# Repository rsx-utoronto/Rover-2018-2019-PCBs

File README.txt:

PCB Repo:

1. Ensure when working, the forward / back annotation is allowed. (A bar in black and yellow stripes will appear at the top of the window if the annotation has broken)
2. Do not have two people working on a board at the same time - merging is hard. (At least until we figure out how to merge nicely)

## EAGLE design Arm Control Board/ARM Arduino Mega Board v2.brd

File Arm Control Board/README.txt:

Board and Schematic for the 2018-2019 Arm control Board

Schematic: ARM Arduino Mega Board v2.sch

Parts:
ARDUINO_DUE1: ARDUINO_DUE_SHIELD
C1, C2: C-US050-045X075; C050-045X075
IC1: 7805TV; TO220V
JP1, JP2, JP3, JP4, JP5, JP12, JP13: PINHD-1X2; 1X02
LED1, LED2, LED3, LED4, LED5, LED6, LED7: LEDCHIP-LED0603; CHIP-LED0603
M-1, M-2, M-3, M-4, M-5, M-6, M-7: PINHD-1X8; 1X08
MD_OUT_1, MD_OUT_2, MD_OUT_3, MD_OUT_4, MD_OUT_5, MD_OUT_6, MD_OUT_7: PINHD-1X8; 1X08
R1, R2, R5, R6, R7, R8, R9, R12, R13, R14, R15, R16, R17, R18: 25K; R0603
R3, R4: 100K; R0603
S1, S2, S3, S4, S5, S6, S7: DS01E; DS-01
U$1: MEGA-FIT_RA_2
U$2: 14PINULTRAFIT
U$3: 4PIN_ULTRA_FIT

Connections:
3V3: ARDUINO_DUE1.3V3, S1.1, S2.1, S3.1, S4.1, S5.1, S6.1, S7.1
5V: ARDUINO_DUE1.5V0 (5V), R3.2, R4.2, U$3.PIN3
D0: ARDUINO_DUE1.0 (RX0<0), MD_OUT_7.2
D1: ARDUINO_DUE1.1 (TX0>1), MD_OUT_6.2
D2: ARDUINO_DUE1.2, MD_OUT_7.3
D3: ARDUINO_DUE1.3, MD_OUT_6.3
D4: ARDUINO_DUE1.4, MD_OUT_5.2
D5: ARDUINO_DUE1.5, MD_OUT_5.3
D6: ARDUINO_DUE1.6, MD_OUT_4.2
D7: ARDUINO_DUE1.7, MD_OUT_4.3
D8: ARDUINO_DUE1.8, MD_OUT_3.2
D9: ARDUINO_DUE1.9, MD_OUT_3.3
D10: ARDUINO_DUE1.10, MD_OUT_2.2
D11: ARDUINO_DUE1.11, MD_OUT_2.3
D12: ARDUINO_DUE1.12, MD_OUT_1.2
D13: ARDUINO_DUE1.13, MD_OUT_1.3
D14: ARDUINO_DUE1.14 (TX3_14)
D15: ARDUINO_DUE1.15 (RX3_15)
D22: ARDUINO_DUE1.22
D23: ARDUINO_DUE1.23
D24: ARDUINO_DUE1.24
D25: ARDUINO_DUE1.25
D26: ARDUINO_DUE1.26
D27: ARDUINO_DUE1.27
D28: ARDUINO_DUE1.28
D29: ARDUINO_DUE1.29
D30: ARDUINO_DUE1.30
D31: ARDUINO_DUE1.31
D32: ARDUINO_DUE1.32
D33: ARDUINO_DUE1.33
D34: ARDUINO_DUE1.34
D35: ARDUINO_DUE1.35
GND: ARDUINO_DUE1.GND, C1.2, C2.2, IC1.2 (GND), JP1.2, JP2.2, JP3.2, JP4.2, JP5.2, JP12.2, JP13.2, LED1.C, LED2.C, LED3.C, LED4.C, LED5.C, LED6.C, LED7.C, M-1.1, M-1.2, M-2.1, M-2.2, M-3.1, M-3.2, M-4.1, M-4.2, M-5.1, M-5.2, M-6.1, M-6.2, M-7.1, M-7.2, MD_OUT_1.1, MD_OUT_2.1, MD_OUT_3.1, MD_OUT_4.1, MD_OUT_5.1, MD_OUT_6.1, MD_OUT_7.1, R12.2, R13.2, R14.2, R15.2, R16.2, R17.2, R18.2, U$1.P$2, U$3.PIN1
N1: MD_OUT_2.4, R8.1, S6.2
N2: MD_OUT_3.4, R7.1, S5.2
N3: MD_OUT_4.4, R6.1, S4.2
N4: MD_OUT_5.4, R5.1, S3.2
N5: MD_OUT_6.4, R2.1, S2.2
N6: MD_OUT_7.4, R1.1, S1.2
N7: MD_OUT_1.4, R9.1, S7.2
unnamed: LED1.A, R1.2
unnamed: LED2.A, R2.2
unnamed: JP1.1, R12.1
unnamed: JP2.1, R13.1
unnamed: JP3.1, R14.1
unnamed: JP4.1, R15.1
unnamed: JP5.1, R16.1
unnamed: JP12.1, R17.1
unnamed: JP13.1, R18.1
unnamed: LED3.A, R5.2
unnamed: LED4.A, R6.2
unnamed: LED5.A, R7.2
unnamed: LED6.A, R8.2
unnamed: LED7.A, R9.2
OUTA1: M-1.5, M-1.6, U$2.PIN5
OUTA2: M-2.5, M-2.6, U$2.PIN1
OUTA3: M-3.5, M-3.6, U$2.PIN4
OUTA4: M-4.5, M-4.6, U$2.PIN8
OUTA5: M-5.5, M-5.6, U$2.PIN12
OUTA6: M-6.5, M-6.6, U$2.PIN13
OUTA7: M-7.5, M-7.6, U$2.PIN9
OUTB1: M-1.3, M-1.4, U$2.PIN7
OUTB2: M-2.3, M-2.4, U$2.PIN3
OUTB3: M-3.3, M-3.4, U$2.PIN2
OUTB4: M-4.3, M-4.4, U$2.PIN6
OUTB5: M-5.3, M-5.4, U$2.PIN10
OUTB6: M-6.3, M-6.4, U$2.PIN14
OUTB7: M-7.3, M-7.4, U$2.PIN11
SCL_OUT: ARDUINO_DUE1.21 (SCL_21), R3.1, U$3.PIN4
SDA_OUT: ARDUINO_DUE1.20 (SDA_20), R4.1, U$3.PIN2
V+: C2.1, IC1.1 (VI), M-1.7, M-1.8, M-2.7, M-2.8, M-3.7, M-3.8, M-4.7, M-4.8, M-5.7, M-5.8, M-6.7, M-6.8, M-7.7, M-7.8, U$1.P$1
VIN: ARDUINO_DUE1.VIN, C1.1, IC1.3 (VO)

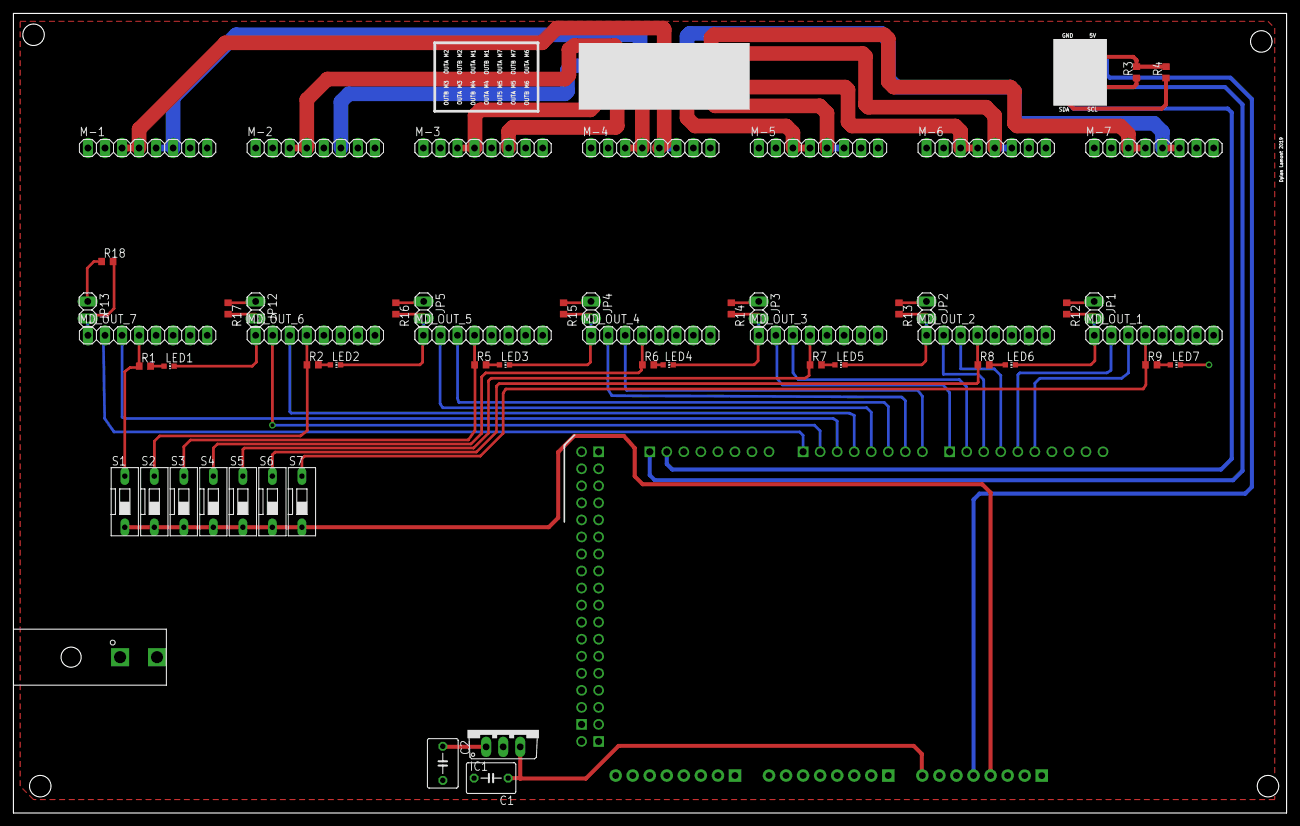
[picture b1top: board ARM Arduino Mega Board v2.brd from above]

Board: 2 copper layers, 189.8 x 119.2 mm, 58 parts (1 on the bottom side), 56 nets.

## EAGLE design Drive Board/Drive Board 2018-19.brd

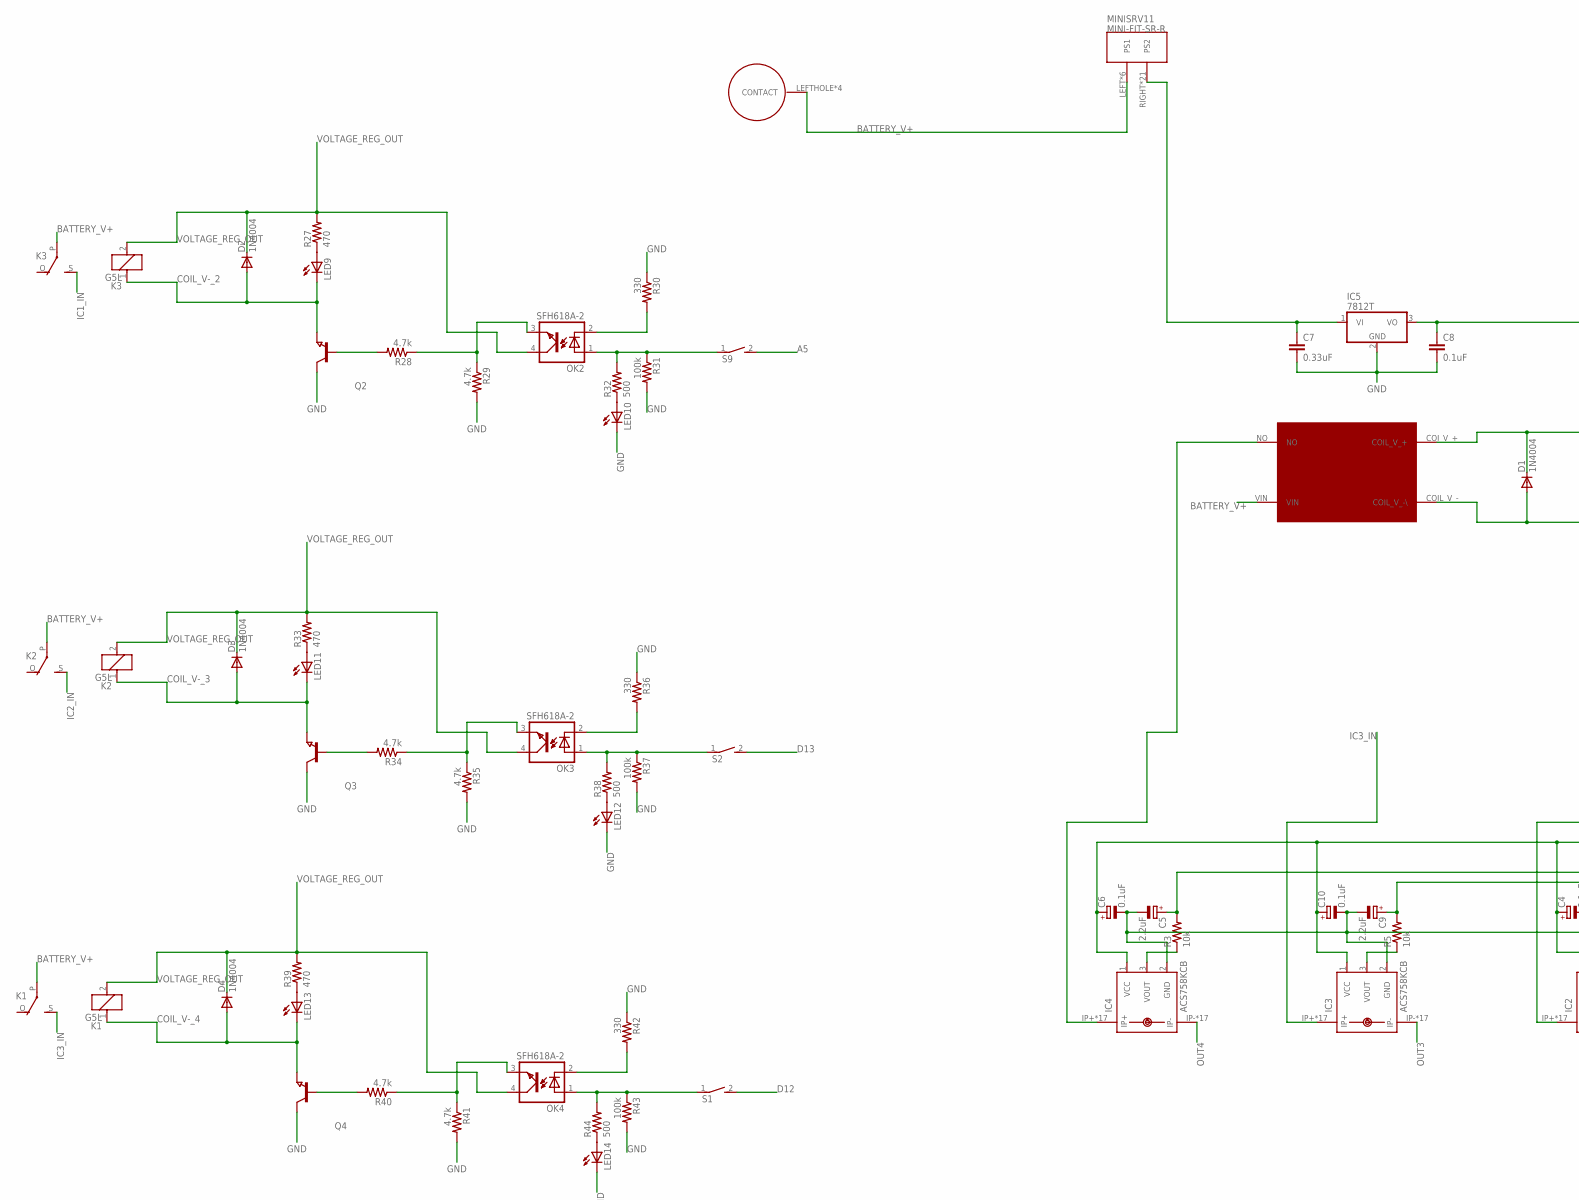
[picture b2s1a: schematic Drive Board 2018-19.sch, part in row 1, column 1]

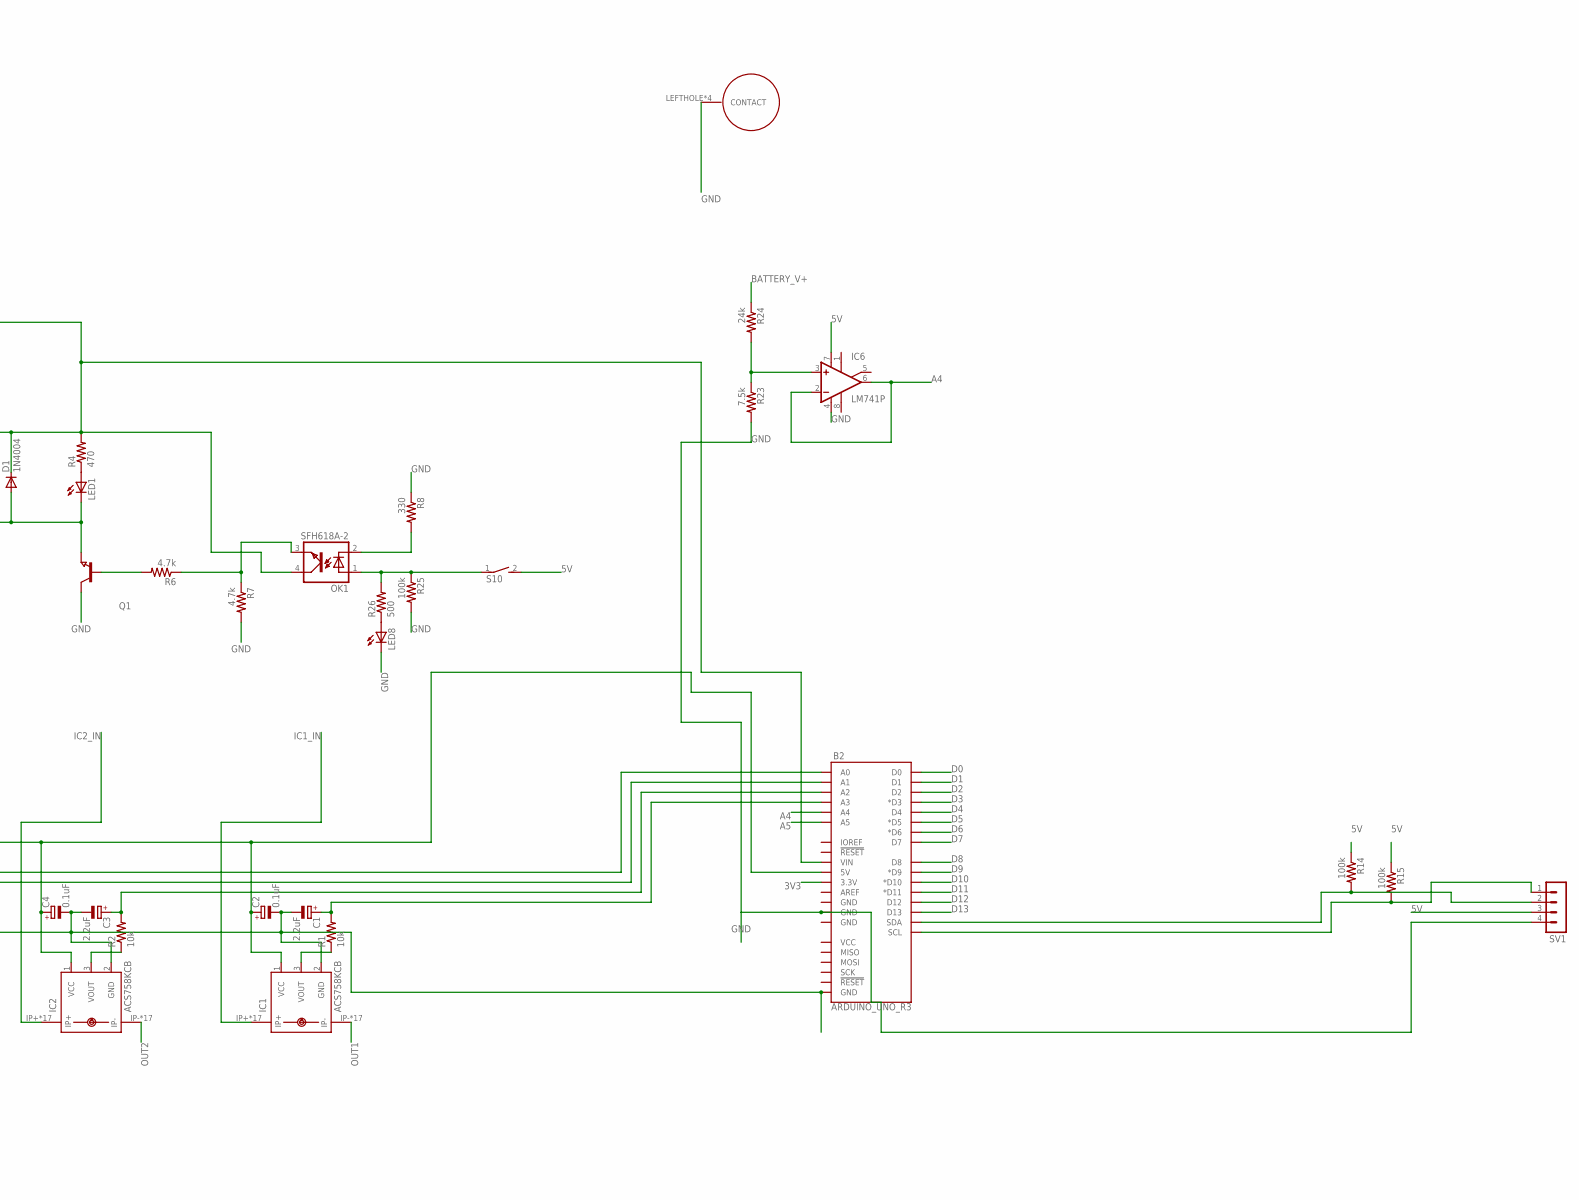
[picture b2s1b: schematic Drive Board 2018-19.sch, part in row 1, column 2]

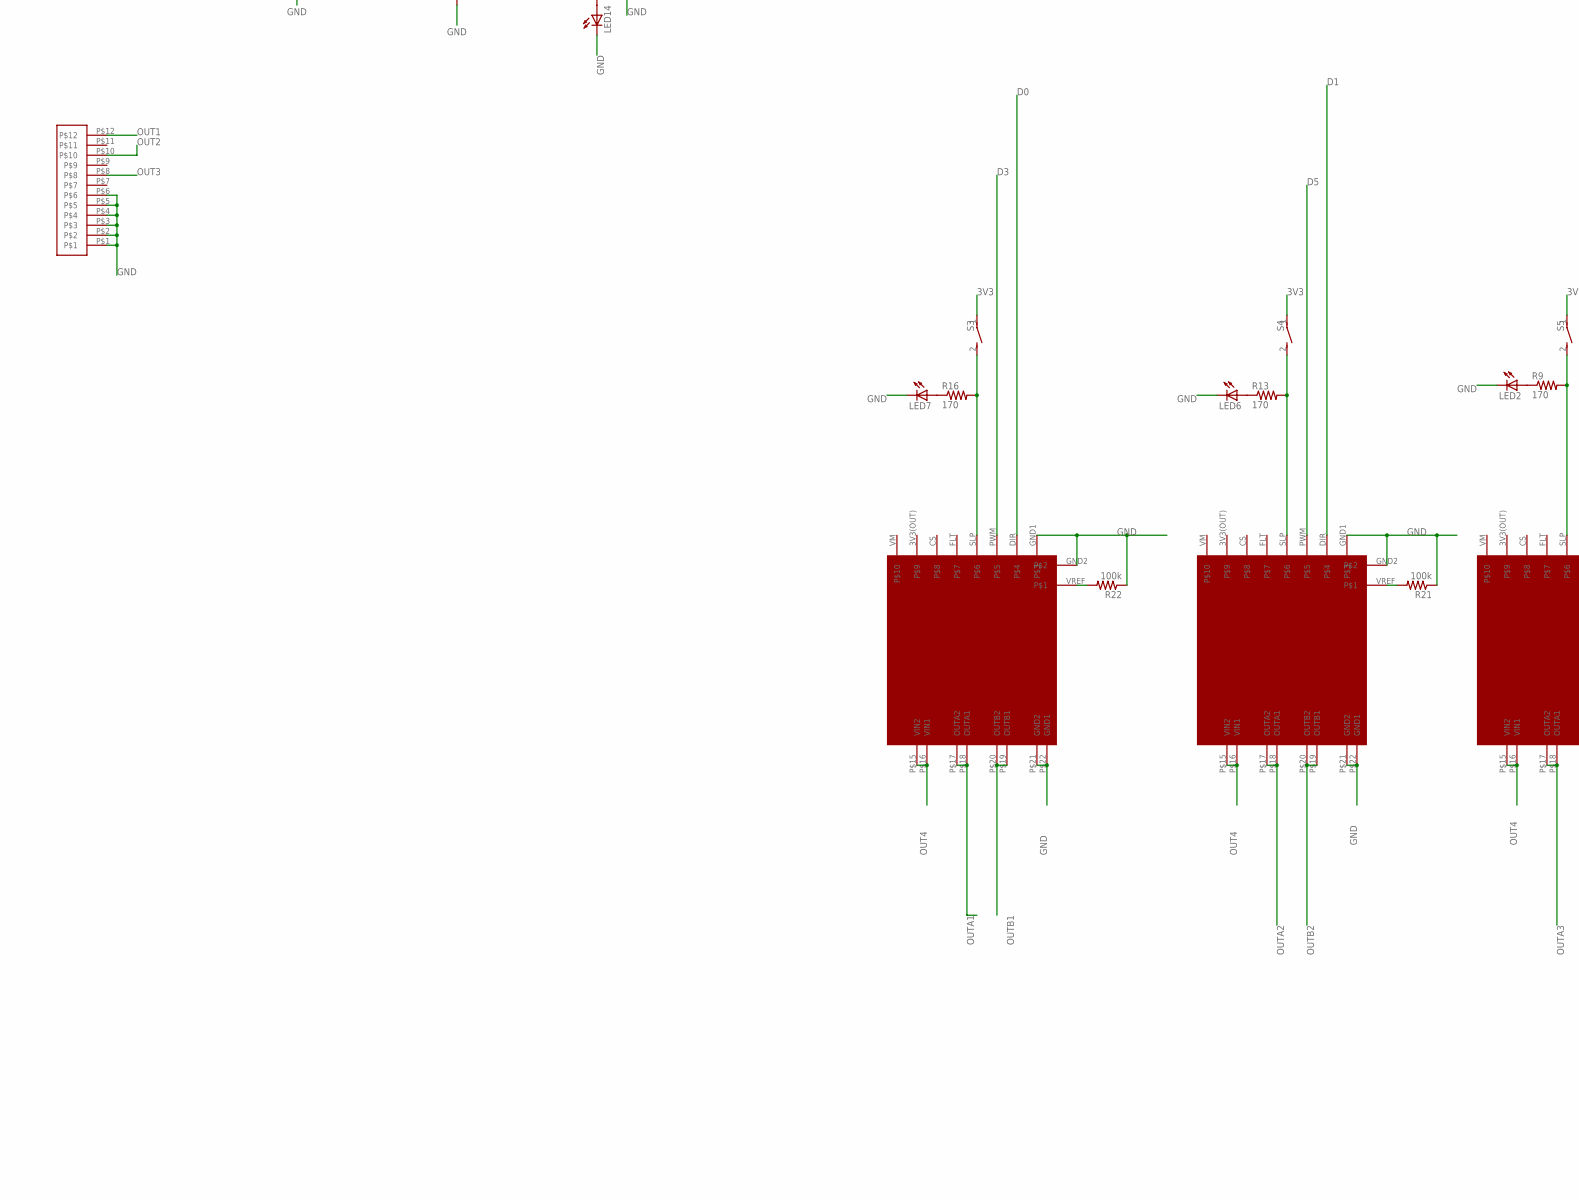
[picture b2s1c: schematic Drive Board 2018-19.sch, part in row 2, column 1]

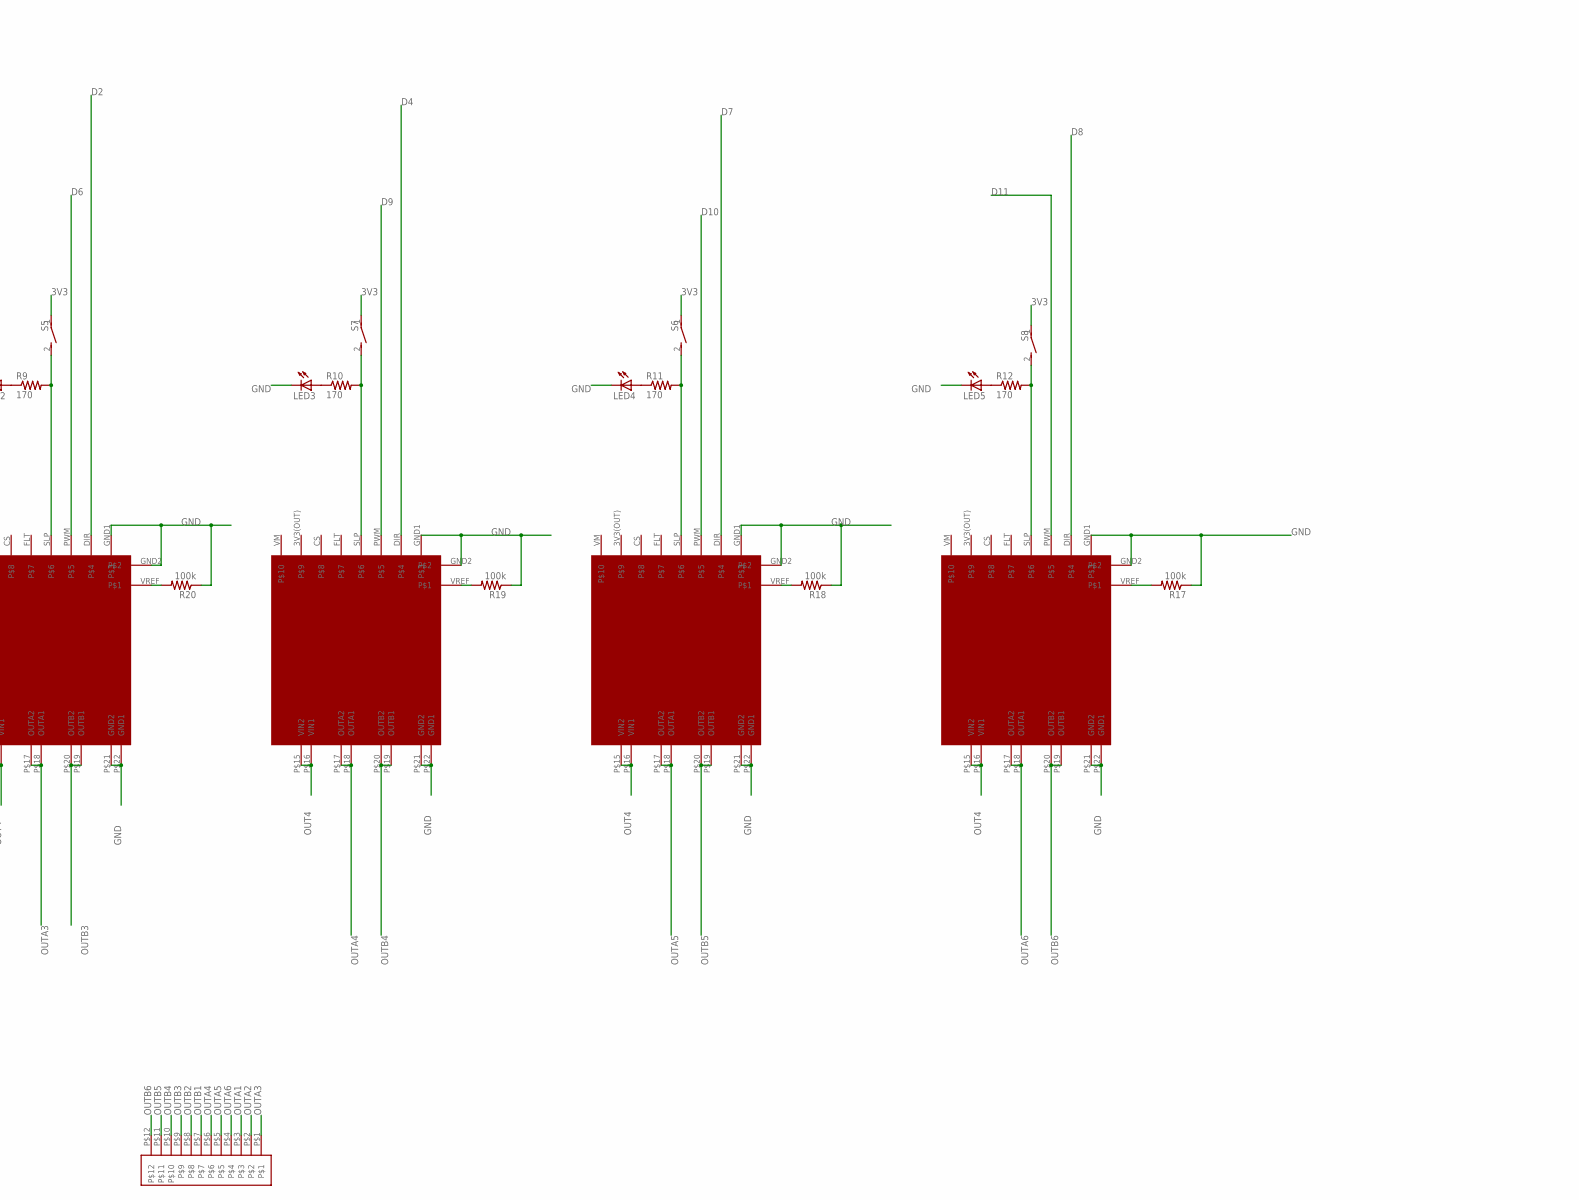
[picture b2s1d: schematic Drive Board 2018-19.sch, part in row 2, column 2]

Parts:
B2: ARDUINO_UNO_R3; ARDUINO_R3
C1, C3, C5, C9: 2.2uF; E2,5-6
C2, C4, C6, C10: 0.1uF; E2,5-6
C7: 0.33uF; C5B5.5
C8: 0.1uF; C5B5.5
D1, D2, D3, D4: 1N4004; DO41-10
IC1, IC2, IC3, IC4: ACS758KCB; CB-PFF
IC5: 7812T; TO220H
IC6: LM741P; DIL08
K1, K2, K3: G5L; G5LE
LED1, LED2, LED3, LED4, LED5, LED6, LED7, LED8, LED9, LED10, LED11, LED12, LED13, LED14: LED_E; LED_1206
MINISRV11: MINI-FIT-SR-R
OK1, OK2, OK3, OK4: SFH618A-2; DIP4
Q1, Q2, Q3, Q4: NPN-TRANSISTOR_SOT23; SOT23
R1, R2, R3, R5: 10k; 0204/7
R4, R27, R33, R39: 470; 0207/10
R6, R7, R28, R29, R34, R35, R40, R41: 4.7k; 0207/10
R8, R30, R36, R42: 330; 0207/10
R9, R10, R11, R12, R13, R16: 170; 0207/10
R14, R15, R17, R18, R19, R20, R21, R22, R25, R31, R37, R43: 100k; 0207/10
R23: 7.5k; 0207/10
R24: 24k; 0207/10
R26, R32, R38, R44: 500; 0207/10
S1, S2, S3, S4, S5, S6, S7, S8, S9, S10: DS01E; DS-01
SV1: MA04-1
U$1, U$2, U$3, U$4, U$5, U$6: HPMD18V17
U$7, U$9: BUSBAR_MOUNT
U$11: JTN1AS-PA-F-DC12V
U$12, U$13: MEGA-FIT_RA_12

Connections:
3V3: B2.3.3V, S3.1, S4.1, S5.1, S6.1, S7.1, S8.1
5V: B2.5V, C2.+, C4.+, C6.+, C10.+, IC1.1 (VCC), IC2.1 (VCC), IC3.1 (VCC), IC4.1 (VCC), IC6.7 (V+), R14.1, R15.1, S10.2, SV1.3
A4: B2.A4, IC6.2 (-IN), IC6.6 (OUT)
A5: B2.A5, S9.2
BATTERY_V+: K1.P, K2.P, K3.P, MINISRV11.LEFT (PS1), MINISRV11.LEFT@1 (PS1), MINISRV11.LEFT@2 (PS1), MINISRV11.LEFT@3 (PS1), MINISRV11.LEFT@4 (PS1), MINISRV11.LEFT@5 (PS1), R24.1, U$7.LEFTHOLE, U$7.P$1, U$7.P$2, U$7.RIGHTHOLE, U$11.VIN
COIL_V-_1: D1.A, LED1.C, Q1.2 (E), U$11.COIL_V_- (COIL_V_-\)
COIL_V-_2: D2.A, K3.1, LED9.C, Q2.2 (E)
COIL_V-_3: D3.A, K2.1, LED11.C, Q3.2 (E)
COIL_V-_4: D4.A, K1.1, LED13.C, Q4.2 (E)
D0: B2.D0, U$1.DIR
D1: B2.D1, U$2.DIR
D2: B2.D2, U$3.DIR
D3: B2.D3 (*D3), U$1.PWM
D4: B2.D4, U$4.DIR
D5: B2.D5 (*D5), U$2.PWM
D6: B2.D6 (*D6), U$3.PWM
D7: B2.D7, U$5.DIR
D8: B2.D8, U$6.DIR
D9: B2.D9 (*D9), U$4.PWM
D10: B2.D10 (*D10), U$5.PWM
D11: B2.D11 (*D11), U$6.PWM
D12: B2.D12, S1.2
D13: B2.D13, S2.2
ESTOP: C7.1, IC5.1 (VI), MINISRV11.RIGHT (PS2), MINISRV11.RIGHT@1 (PS2), MINISRV11.RIGHT@2 (PS2), MINISRV11.RIGHT@3 (PS2), MINISRV11.RIGHT@4 (PS2), MINISRV11.RIGHT@5 (PS2), MINISRV11.RIGHT@6 (PS2), MINISRV11.RIGHT@7 (PS2), MINISRV11.RIGHT@8 (PS2), MINISRV11.RIGHT@9 (PS2), MINISRV11.RIGHT@10 (PS2), MINISRV11.RIGHT@11 (PS2), MINISRV11.RIGHT@12 (PS2), MINISRV11.RIGHT@13 (PS2), MINISRV11.RIGHT@14 (PS2), MINISRV11.RIGHT@15 (PS2), MINISRV11.RIGHT@16 (PS2), MINISRV11.RIGHT@17 (PS2), MINISRV11.RIGHT@18 (PS2), MINISRV11.RIGHT@19 (PS2), MINISRV11.RIGHT@20 (PS2)
GND: B2.GND@1 (GND), B2.GND@3 (GND), C1.-, C2.-, C3.-, C4.-, C5.-, C6.-, C7.2, C8.2, C9.-, C10.-, IC1.2 (GND), IC2.2 (GND), IC3.2 (GND), IC4.2 (GND), IC5.2 (GND), IC6.4 (V-), LED2.C, LED3.C, LED4.C, LED5.C, LED6.C, LED7.C, LED8.C, LED10.C, LED12.C, LED14.C, Q1.3 (C), Q2.3 (C), Q3.3 (C), Q4.3 (C), R7.2, R8.1, R17.1, R18.1, R19.1, R20.1, R21.1, R22.1, R23.2, R25.2, R29.2, R30.1, R31.2, R35.2, R36.1, R37.2, R41.2, R42.1, R43.2, SV1.4, U$1.GND1, U$1.GND2, U$1.P$21 (GND2), U$1.P$22 (GND1), U$2.GND1, U$2.GND2, U$2.P$21 (GND2), U$2.P$22 (GND1), U$3.GND1, U$3.GND2, U$3.P$21 (GND2), U$3.P$22 (GND1), U$4.GND1, U$4.GND2, U$4.P$21 (GND2), U$4.P$22 (GND1), U$5.GND1, U$5.GND2, U$5.P$21 (GND2), U$5.P$22 (GND1), U$6.GND1, U$6.GND2, U$6.P$21 (GND2), U$6.P$22 (GND1), U$9.LEFTHOLE, U$9.P$1, U$9.P$2, U$9.RIGHTHOLE, U$13.P$1, U$13.P$2, U$13.P$3, U$13.P$4, U$13.P$5, U$13.P$6
IC1_IN: IC1.IP+, IC1.IP+@2 (IP+), IC1.IP+@3 (IP+), IC1.IP+@4 (IP+), IC1.IP+@5 (IP+), IC1.IP+@6 (IP+), IC1.IP+@7 (IP+), IC1.IP+@8 (IP+), IC1.IP+@9 (IP+), IC1.IP+@10 (IP+), IC1.IP+@11 (IP+), IC1.IP+@12 (IP+), IC1.IP+@13 (IP+), IC1.IP+@14 (IP+), IC1.IP+@15 (IP+), IC1.IP+@16 (IP+), IC1.IP+@17 (IP+), K3.S
IC2_IN: IC2.IP+, IC2.IP+@2 (IP+), IC2.IP+@3 (IP+), IC2.IP+@4 (IP+), IC2.IP+@5 (IP+), IC2.IP+@6 (IP+), IC2.IP+@7 (IP+), IC2.IP+@8 (IP+), IC2.IP+@9 (IP+), IC2.IP+@10 (IP+), IC2.IP+@11 (IP+), IC2.IP+@12 (IP+), IC2.IP+@13 (IP+), IC2.IP+@14 (IP+), IC2.IP+@15 (IP+), IC2.IP+@16 (IP+), IC2.IP+@17 (IP+), K2.S
IC3_IN: IC3.IP+, IC3.IP+@2 (IP+), IC3.IP+@3 (IP+), IC3.IP+@4 (IP+), IC3.IP+@5 (IP+), IC3.IP+@6 (IP+), IC3.IP+@7 (IP+), IC3.IP+@8 (IP+), IC3.IP+@9 (IP+), IC3.IP+@10 (IP+), IC3.IP+@11 (IP+), IC3.IP+@12 (IP+), IC3.IP+@13 (IP+), IC3.IP+@14 (IP+), IC3.IP+@15 (IP+), IC3.IP+@16 (IP+), IC3.IP+@17 (IP+), K1.S
unnamed: LED8.A, R26.1
unnamed: IC1.3 (VOUT), R1.1
unnamed: LED1.A, R4.1
unnamed: B2.A3, C1.+, R1.2
unnamed: IC6.3 (+IN), R23.1, R24.2
unnamed: IC2.3 (VOUT), R2.1
unnamed: LED9.A, R27.1
unnamed: B2.A2, C3.+, R2.2
unnamed: Q2.1 (B), R28.2
unnamed: IC4.3 (VOUT), R3.1
unnamed: OK2.3 (EMIT), R28.1, R29.1
unnamed: OK2.2 (C), R30.2
unnamed: B2.A1, C9.+, R5.2
unnamed: LED10.A, R32.1
unnamed: LED11.A, R33.1
unnamed: Q1.1 (B), R6.2
unnamed: IC3.3 (VOUT), R5.1
unnamed: Q3.1 (B), R34.2
unnamed: B2.A0, C5.+, R3.2
unnamed: OK3.3 (EMIT), R34.1, R35.1
unnamed: OK1.3 (EMIT), R6.1, R7.1
unnamed: OK3.2 (C), R36.2
unnamed: LED12.A, R38.1
unnamed: IC4.IP+, IC4.IP+@2 (IP+), IC4.IP+@3 (IP+), IC4.IP+@4 (IP+), IC4.IP+@5 (IP+), IC4.IP+@6 (IP+), IC4.IP+@7 (IP+), IC4.IP+@8 (IP+), IC4.IP+@9 (IP+), IC4.IP+@10 (IP+), IC4.IP+@11 (IP+), IC4.IP+@12 (IP+), IC4.IP+@13 (IP+), IC4.IP+@14 (IP+), IC4.IP+@15 (IP+), IC4.IP+@16 (IP+), IC4.IP+@17 (IP+), U$11.NO
unnamed: LED13.A, R39.1
unnamed: Q4.1 (B), R40.2
unnamed: OK4.3 (EMIT), R40.1, R41.1
unnamed: OK4.2 (C), R42.2
unnamed: LED14.A, R44.1
unnamed: OK1.2 (C), R8.2
unnamed: R18.2, U$5.VREF
unnamed: R20.2, U$3.VREF
unnamed: LED2.A, R9.1
unnamed: R17.2, U$6.VREF
unnamed: B2.SCL, R15.2, SV1.1
unnamed: B2.SDA, R14.2, SV1.2
unnamed: LED3.A, R10.1
unnamed: LED4.A, R11.1
unnamed: LED5.A, R12.1
unnamed: R19.2, U$4.VREF
unnamed: LED6.A, R13.1
unnamed: LED7.A, R16.1
unnamed: R21.2, U$2.VREF
unnamed: R22.2, U$1.VREF
unnamed: R12.2, S8.2, U$6.SLP
unnamed: R11.2, S6.2, U$5.SLP
unnamed: R10.2, S7.2, U$4.SLP
unnamed: R9.2, S5.2, U$3.SLP
unnamed: R13.2, S4.2, U$2.SLP
unnamed: R16.2, S3.2, U$1.SLP
OPTO1: OK2.1 (A), R31.1, R32.2, S9.1
OPTO2: OK3.1 (A), R37.1, R38.2, S2.1
OPTO3: OK4.1 (A), R43.1, R44.2, S1.1
OPTO4: OK1.1 (A), R25.1, R26.2, S10.1
OUT1: IC1.IP-, IC1.IP-@2 (IP-), IC1.IP-@3 (IP-), IC1.IP-@4 (IP-), IC1.IP-@5 (IP-), IC1.IP-@6 (IP-), IC1.IP-@7 (IP-), IC1.IP-@8 (IP-), IC1.IP-@9 (IP-), IC1.IP-@10 (IP-), IC1.IP-@11 (IP-), IC1.IP-@12 (IP-), IC1.IP-@13 (IP-), IC1.IP-@14 (IP-), IC1.IP-@15 (IP-), IC1.IP-@16 (IP-), IC1.IP-@17 (IP-), U$13.P$12
OUT2: IC2.IP-, IC2.IP-@2 (IP-), IC2.IP-@3 (IP-), IC2.IP-@4 (IP-), IC2.IP-@5 (IP-), IC2.IP-@6 (IP-), IC2.IP-@7 (IP-), IC2.IP-@8 (IP-), IC2.IP-@9 (IP-), IC2.IP-@10 (IP-), IC2.IP-@11 (IP-), IC2.IP-@12 (IP-), IC2.IP-@13 (IP-), IC2.IP-@14 (IP-), IC2.IP-@15 (IP-), IC2.IP-@16 (IP-), IC2.IP-@17 (IP-), U$13.P$10
OUT3: IC3.IP-, IC3.IP-@2 (IP-), IC3.IP-@3 (IP-), IC3.IP-@4 (IP-), IC3.IP-@5 (IP-), IC3.IP-@6 (IP-), IC3.IP-@7 (IP-), IC3.IP-@8 (IP-), IC3.IP-@9 (IP-), IC3.IP-@10 (IP-), IC3.IP-@11 (IP-), IC3.IP-@12 (IP-), IC3.IP-@13 (IP-), IC3.IP-@14 (IP-), IC3.IP-@15 (IP-), IC3.IP-@16 (IP-), IC3.IP-@17 (IP-), U$13.P$8
OUT4: IC4.IP-, IC4.IP-@2 (IP-), IC4.IP-@3 (IP-), IC4.IP-@4 (IP-), IC4.IP-@5 (IP-), IC4.IP-@6 (IP-), IC4.IP-@7 (IP-), IC4.IP-@8 (IP-), IC4.IP-@9 (IP-), IC4.IP-@10 (IP-), IC4.IP-@11 (IP-), IC4.IP-@12 (IP-), IC4.IP-@13 (IP-), IC4.IP-@14 (IP-), IC4.IP-@15 (IP-), IC4.IP-@16 (IP-), IC4.IP-@17 (IP-), U$1.P$15 (VIN2), U$1.P$16 (VIN1), U$2.P$15 (VIN2), U$2.P$16 (VIN1), U$3.P$15 (VIN2), U$3.P$16 (VIN1), U$4.P$15 (VIN2), U$4.P$16 (VIN1), U$5.P$15 (VIN2), U$5.P$16 (VIN1), U$6.P$15 (VIN2), U$6.P$16 (VIN1)
OUTA1: U$1.P$17 (OUTA2), U$1.P$18 (OUTA1), U$12.P$3
OUTA2: U$2.P$17 (OUTA2), U$2.P$18 (OUTA1), U$12.P$2
OUTA3: U$3.P$17 (OUTA2), U$3.P$18 (OUTA1), U$12.P$1
OUTA4: U$4.P$17 (OUTA2), U$4.P$18 (OUTA1), U$12.P$6
OUTA5: U$5.P$17 (OUTA2), U$5.P$18 (OUTA1), U$12.P$5
OUTA6: U$6.P$17 (OUTA2), U$6.P$18 (OUTA1), U$12.P$4
OUTB1: U$1.P$19 (OUTB1), U$1.P$20 (OUTB2), U$12.P$7
OUTB2: U$2.P$19 (OUTB1), U$2.P$20 (OUTB2), U$12.P$8
OUTB3: U$3.P$19 (OUTB1), U$3.P$20 (OUTB2), U$12.P$9
OUTB4: U$4.P$19 (OUTB1), U$4.P$20 (OUTB2), U$12.P$10
OUTB5: U$5.P$19 (OUTB1), U$5.P$20 (OUTB2), U$12.P$11
OUTB6: U$6.P$19 (OUTB1), U$6.P$20 (OUTB2), U$12.P$12
VOLTAGE_REG_OUT: B2.VIN, C8.1, D1.C, D2.C, D3.C, D4.C, IC5.3 (VO), K1.2, K2.2, K3.2, OK1.4 (COL), OK2.4 (COL), OK3.4 (COL), OK4.4 (COL), R4.2, R27.2, R33.2, R39.2, U$11.COI_V_+ (COIL_V_+)

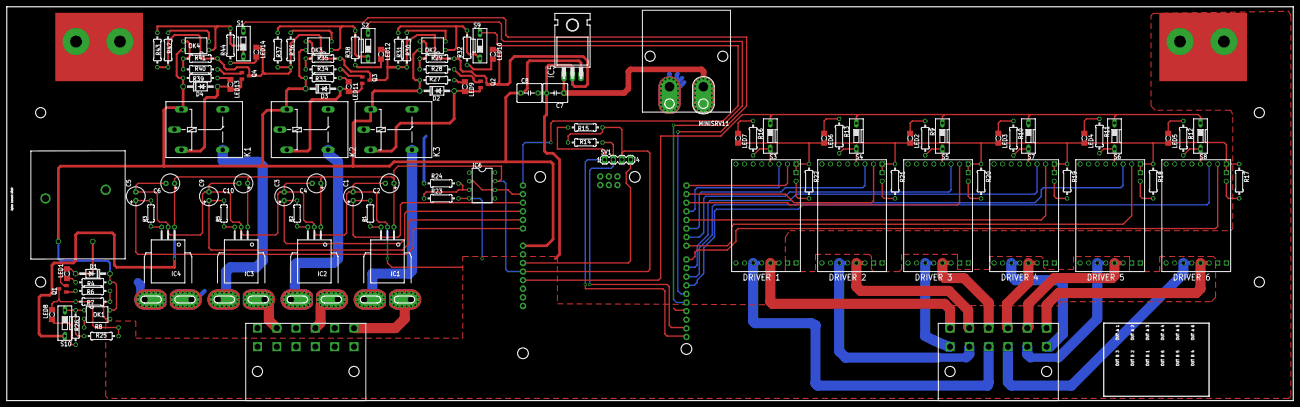
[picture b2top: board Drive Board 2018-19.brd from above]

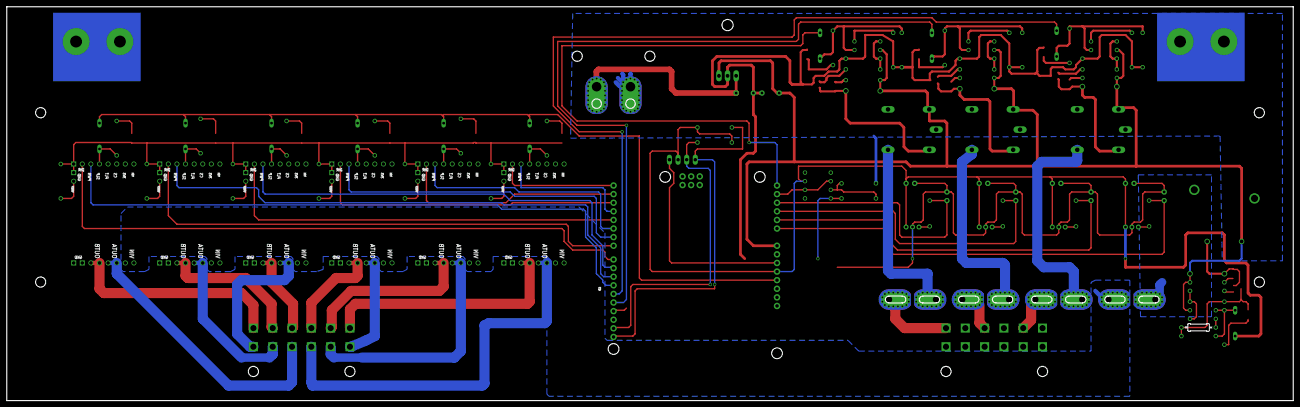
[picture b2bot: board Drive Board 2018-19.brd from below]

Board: 2 copper layers, 379.8 x 116.3 mm, 113 parts (2 on the bottom side), 99 nets.

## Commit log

2019-02-09 Set up Arm Control Board Folder
2019-02-09 Changed board to Mega
2019-02-09 test
2019-02-09 added pull up resistors for i2c
2019-02-09 removed tx and rx
2019-02-09 Placed power connector
2019-02-09 trying to fix conflict
2019-02-09 fixing conflict
2019-02-09 still trying to fix
2019-02-09 this should be fixed
2019-02-16 Added Drive Boards
2019-02-16 Added readme for repo
2019-02-20 deleted old components
    need to change footprint of relay
2019-02-20 Begin prep for new board
2019-02-21 Motor drivers added
2019-02-22 Added Busbar lbr and other power connections to sch
2019-02-23 Started board routing
2019-02-24 first attempt finished for board design
2019-03-02 Re doing layout, just need planes
2019-03-02 Finished First draft
2019-03-06 Fixed optocoupler mismatched pins
2019-03-10 Update from chris meeting
2019-03-10 Added Larger GND Plane
2019-03-11 Change to t aand bstop layers of the bus bar termials
2019-03-11 Fixed Battery bay terminal pad connection
2019-03-11 Fixed Battery terminal pad connection
2019-03-11 Fixed route size for planes
2019-03-11 Fixed overlap of trace for current sensor
2019-03-11 Fixed stray trace overlap
2019-03-11 Fix stray trace
2019-03-11 fixed mixed ground network
2019-03-11 Fixed mixed ground signals
2019-03-16 Arm control Board: mirrored arduino, added switches, added mega fit for power, added motor indicator LEDs, added LM7805 for Arduino power regulation
2019-03-16 Updated the path for the voltage regulator
2019-03-22 Added Components for relay
2019-03-23 Finished Layout for Relay support circuitry
2019-03-25 Relay control from DIO pins implemented
2019-03-27 Added ultrafit connectors
2019-03-27 updated naming scheme
2019-03-28 Updated trace width and added connector information
2019-03-28 Updated Vin plane
2019-03-28 Pin Map for Arm Board
2019-04-07 updated plane thickness
2019-04-07 Gerbers added for drive board and arm control pcb

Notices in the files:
parts and their libraries:
SparkFun-Boards: Licensing: Creative Commons ShareAlike 4.0 International - https://creativecommons.org/licenses/by-sa/4.0
